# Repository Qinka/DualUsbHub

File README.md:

# DualUsbHub
Dual host plugin usb 2.0 HUB

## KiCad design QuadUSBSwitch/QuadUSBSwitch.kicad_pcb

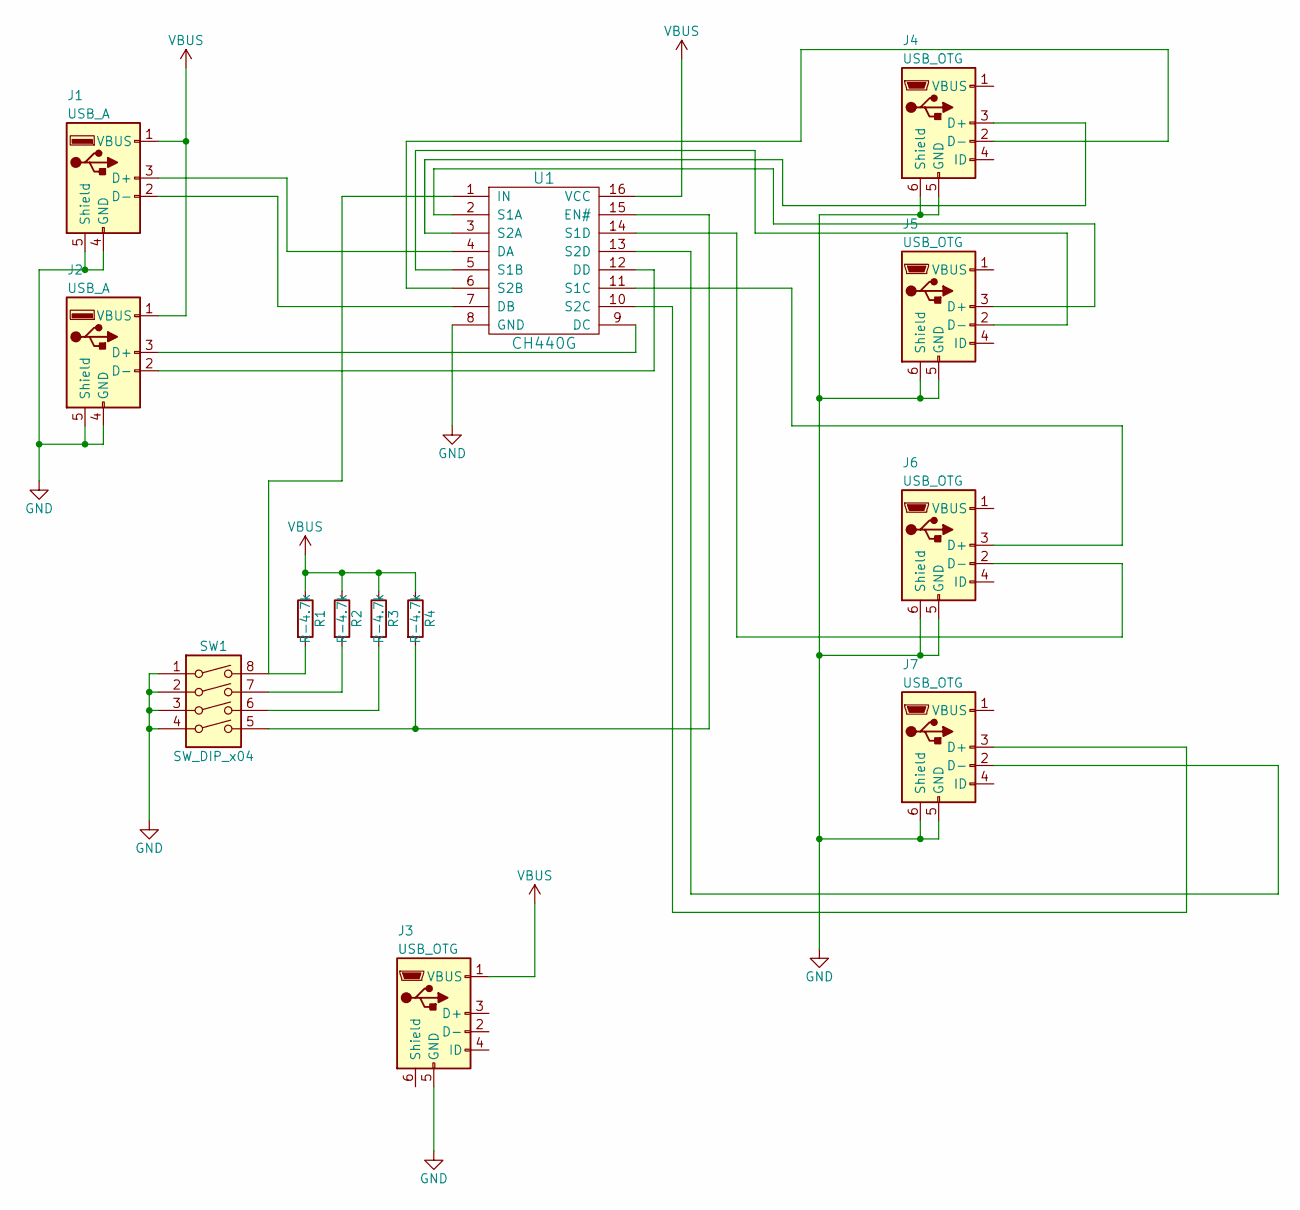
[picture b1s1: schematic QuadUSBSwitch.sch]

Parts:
J1, J2: USB_A
J3, J4, J5, J6, J7: USB_OTG; USB_Micro-B
R1, R2, R3, R4: R-4.7k; R_0805
SW1: SW_DIP_x04; SW_DIP_x4_W8.61mm_Slide_LowProfile
U1: CH440G; ch440g

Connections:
GND: J1.4 (GND), J1.5 (Shield), J2.4 (GND), J2.5 (Shield), J3.5 (GND), J4.5 (GND), J4.6 (Shield), J5.5 (GND), J5.6 (Shield), J6.5 (GND), J6.6 (Shield), J7.5 (GND), J7.6 (Shield), SW1.1, SW1.2, SW1.3, SW1.4, U1.8 (GND)
unnamed: J1.2 (D-), U1.7 (DB)
unnamed: J1.3 (D+), U1.4 (DA)
unnamed: J2.2 (D-), U1.12 (DD)
unnamed: J2.3 (D+), U1.9 (DC)
unnamed: J4.2 (D-), U1.6 (S2B)
unnamed: J4.3 (D+), U1.3 (S2A)
unnamed: J5.2 (D-), U1.5 (S1B)
unnamed: J5.3 (D+), U1.2 (S1A)
unnamed: J6.2 (D-), U1.14 (S1D)
unnamed: J6.3 (D+), U1.11 (S1C)
unnamed: J7.2 (D-), U1.13 (S2D)
unnamed: J7.3 (D+), U1.10 (S2C)
unnamed: R1.2, SW1.8, U1.1 (IN)
unnamed: R2.2, SW1.7
unnamed: R3.2, SW1.6
unnamed: R4.2, SW1.5, U1.15 (EN#)
VBUS: J1.1 (VBUS), J2.1 (VBUS), J3.1 (VBUS), R1.1, R2.1, R3.1, R4.1, U1.16 (VCC)

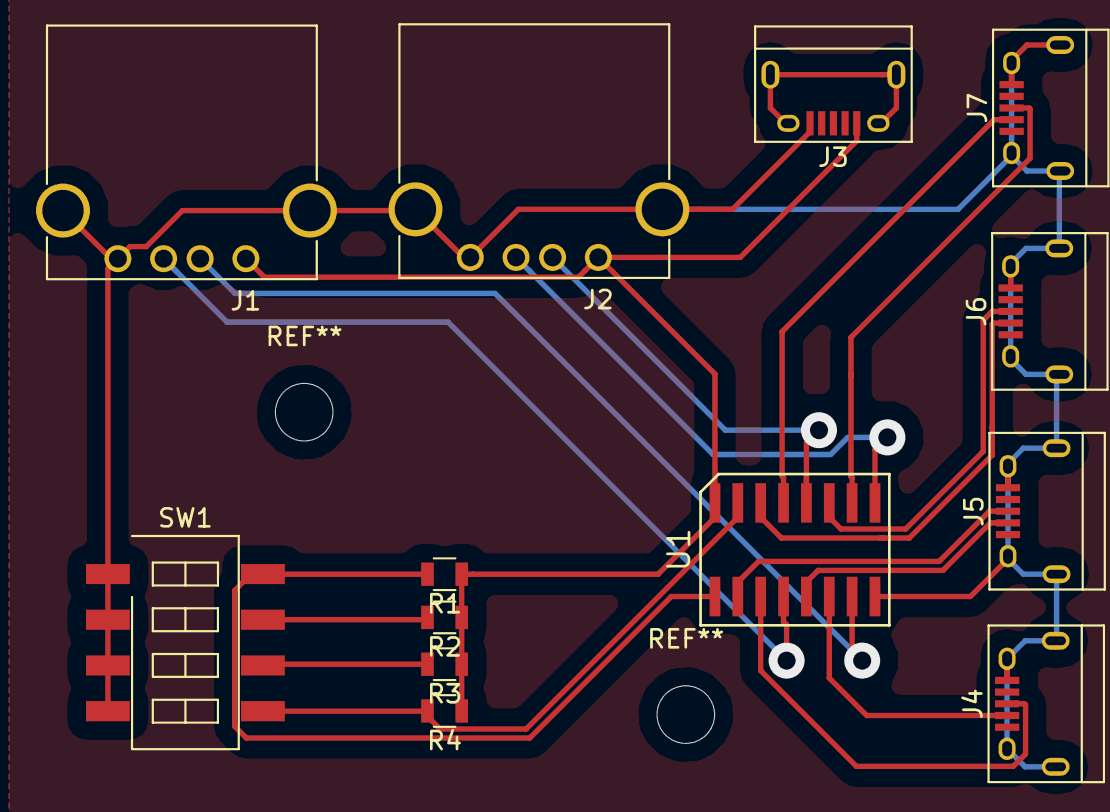
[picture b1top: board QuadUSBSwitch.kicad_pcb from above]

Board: 2 copper layers, 13 parts (0 on the bottom side), 18 nets.

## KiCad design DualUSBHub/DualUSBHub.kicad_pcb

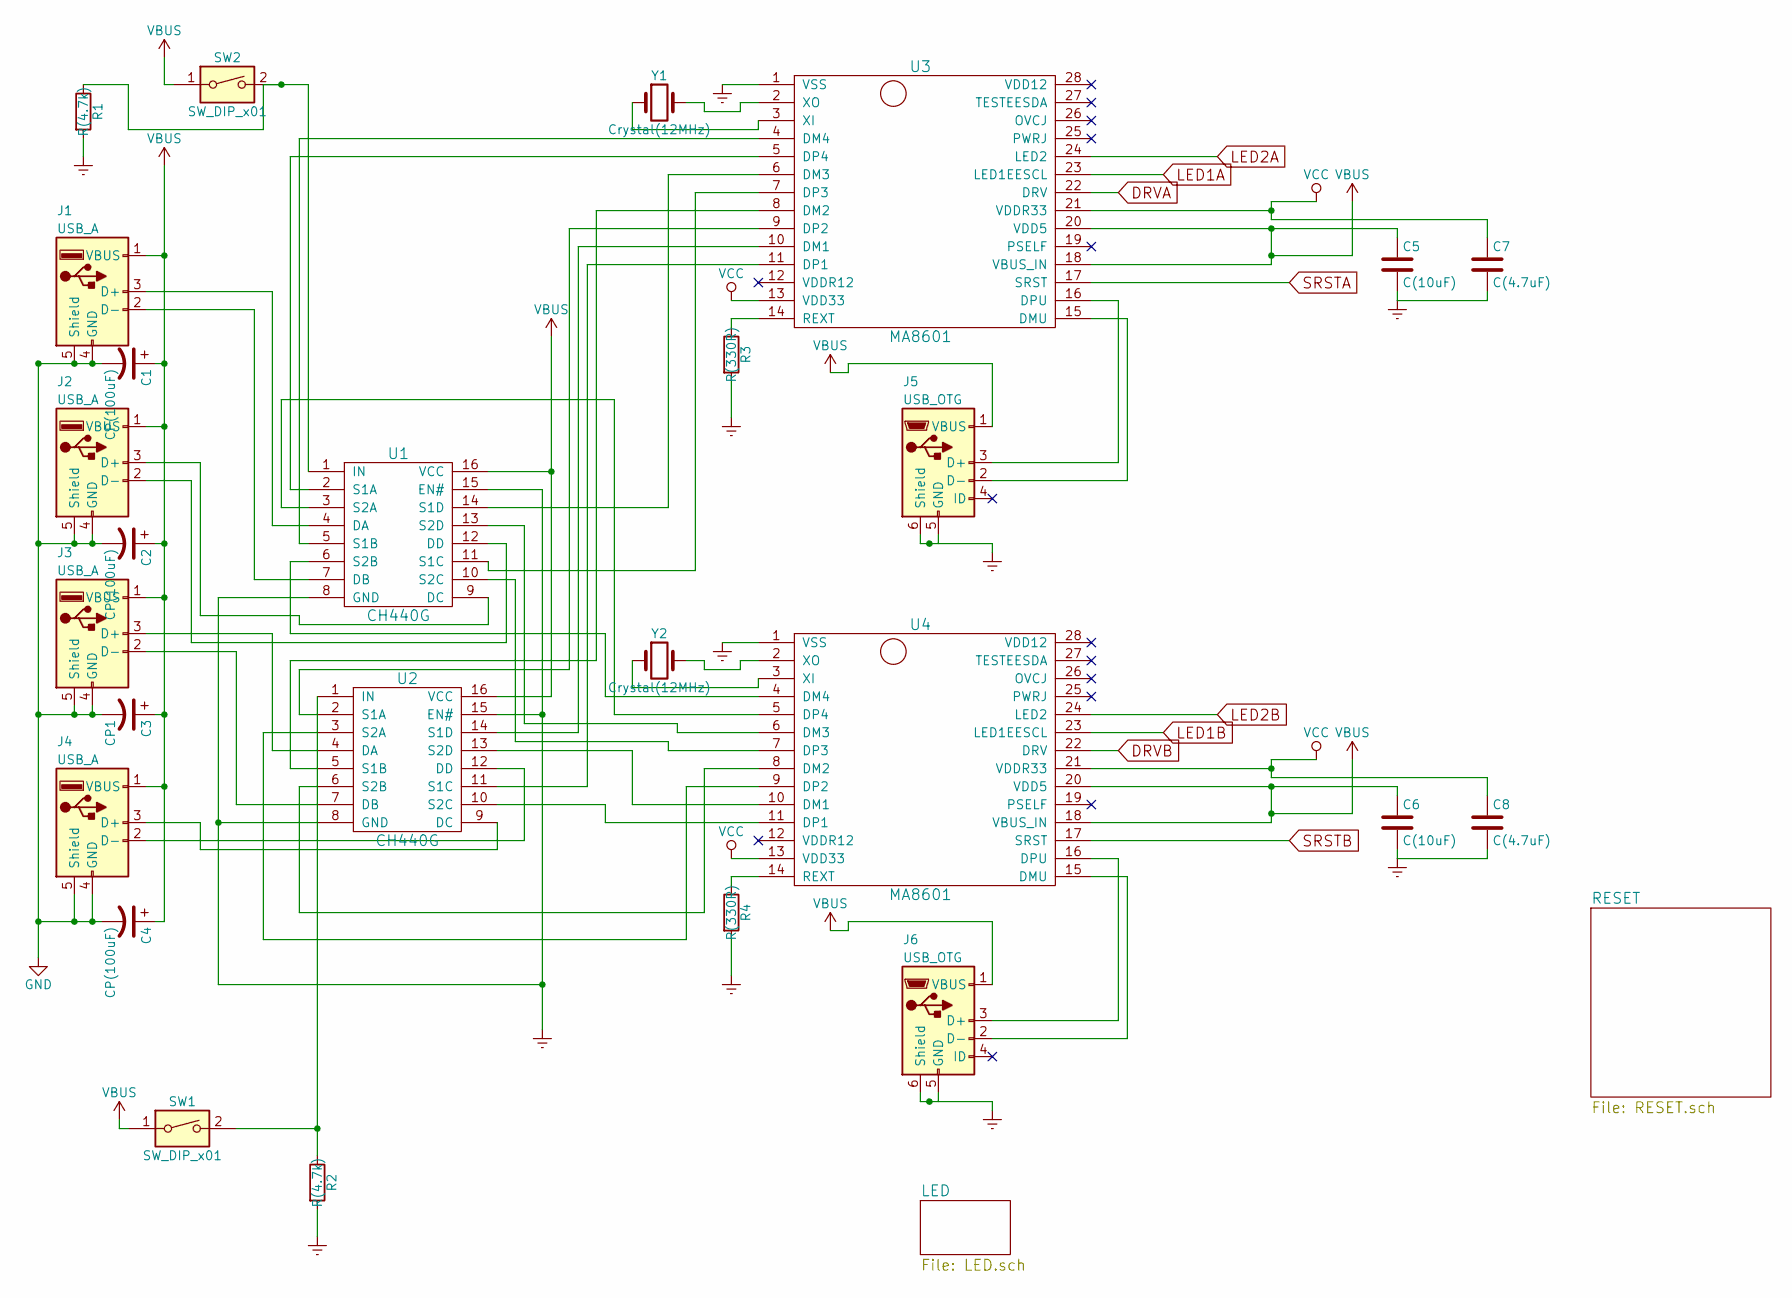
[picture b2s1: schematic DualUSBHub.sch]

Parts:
C1, C2, C4: CP(100uF); CP_Elec_6.3x4.5
C3: CP1; CP_Elec_6.3x4.5
C5, C6: C(10uF); C_0805
C7, C8: C(4.7uF); C_0805
J1, J2, J3, J4: USB_A
J5, J6: USB_OTG; USB_Micro-B
R1, R2: R(4.7k); R_0805
R3, R4: R(330R); R_0805
SW1, SW2: SW_DIP_x01; SW_DIP_x1_W7.62mm_Slide_Copal_CHS-B
U1, U2: CH440G; ch440g
U3, U4: MA8601; ma8601
Y1, Y2: Crystal(12MHz); Crystal_SMD_HC49-SD

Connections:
DRVA: U3.22 (DRV); also elsewhere on the board
DRVB: U4.22 (DRV); also elsewhere on the board
Earth: C5.2, C6.2, C7.2, C8.2, J5.6 (Shield), J6.6 (Shield), R1.2, R2.2, R3.2, R4.2, U1.8 (GND), U1.15 (EN#), U2.8 (GND), U2.15 (EN#), U3.1 (VSS), U4.1 (VSS); also elsewhere on the board
GND: C1.2, C2.2, C3.2, C4.2, J1.4 (GND), J1.5 (Shield), J2.4 (GND), J2.5 (Shield), J3.4 (GND), J3.5 (Shield), J4.4 (GND), J4.5 (Shield)
LED1A: U3.23 (LED1EESCL); also elsewhere on the board
LED1B: U4.23 (LED1EESCL); also elsewhere on the board
LED2A: U3.24 (LED2); also elsewhere on the board
LED2B: U4.24 (LED2); also elsewhere on the board
unnamed: J1.2 (D-), U1.7 (DB)
unnamed: J1.3 (D+), U1.4 (DA)
unnamed: J2.2 (D-), U1.12 (DD)
unnamed: J2.3 (D+), U1.9 (DC)
unnamed: J3.2 (D-), U2.7 (DB)
unnamed: J3.3 (D+), U2.4 (DA)
unnamed: J4.2 (D-), U2.12 (DD)
unnamed: J4.3 (D+), U2.9 (DC)
unnamed: J5.2 (D-), U3.15 (DMU)
unnamed: J5.3 (D+), U3.16 (DPU)
unnamed: J6.2 (D-), U4.15 (DMU)
unnamed: J6.3 (D+), U4.16 (DPU)
unnamed: R1.1, SW2.2, U1.1 (IN)
unnamed: R2.1, SW1.2, U2.1 (IN)
unnamed: R3.1, U3.14 (REXT)
unnamed: R4.1, U4.14 (REXT)
unnamed: U1.2 (S1A), U3.5 (DP4)
unnamed: U1.3 (S2A), U4.5 (DP4)
unnamed: U1.5 (S1B), U3.4 (DM4)
unnamed: U1.6 (S2B), U4.4 (DM4)
unnamed: U1.10 (S2C), U4.7 (DP3)
unnamed: U1.11 (S1C), U3.7 (DP3)
unnamed: U1.13 (S2D), U4.6 (DM3)
unnamed: U1.14 (S1D), U3.6 (DM3)
unnamed: U2.2 (S1A), U3.9 (DP2)
unnamed: U2.3 (S2A), U4.9 (DP2)
unnamed: U2.5 (S1B), U3.8 (DM2)
unnamed: U2.6 (S2B), U4.8 (DM2)
unnamed: U2.10 (S2C), U4.11 (DP1)
unnamed: U2.11 (S1C), U3.11 (DP1)
unnamed: U2.13 (S2D), U4.10 (DM1)
unnamed: U2.14 (S1D), U3.10 (DM1)
unnamed: U3.2 (XO), Y1.2
unnamed: U3.3 (XI), Y1.1
unnamed: U4.2 (XO), Y2.2
unnamed: U4.3 (XI), Y2.1
SRSTA: U3.17 (SRST); also elsewhere on the board
SRSTB: U4.17 (SRST); also elsewhere on the board
VBUS: C1.1, C2.1, C3.1, C4.1, C5.1, C6.1, J1.1 (VBUS), J2.1 (VBUS), J3.1 (VBUS), J4.1 (VBUS), J5.1 (VBUS), J6.1 (VBUS), SW1.1, SW2.1, U1.16 (VCC), U2.16 (VCC), U3.18 (VBUS_IN), U3.20 (VDD5), U4.18 (VBUS_IN), U4.20 (VDD5); also elsewhere on the board
VCC: C7.1, C8.1, U3.13 (VDD33), U3.21 (VDDR33), U4.13 (VDD33), U4.21 (VDDR33); also elsewhere on the board

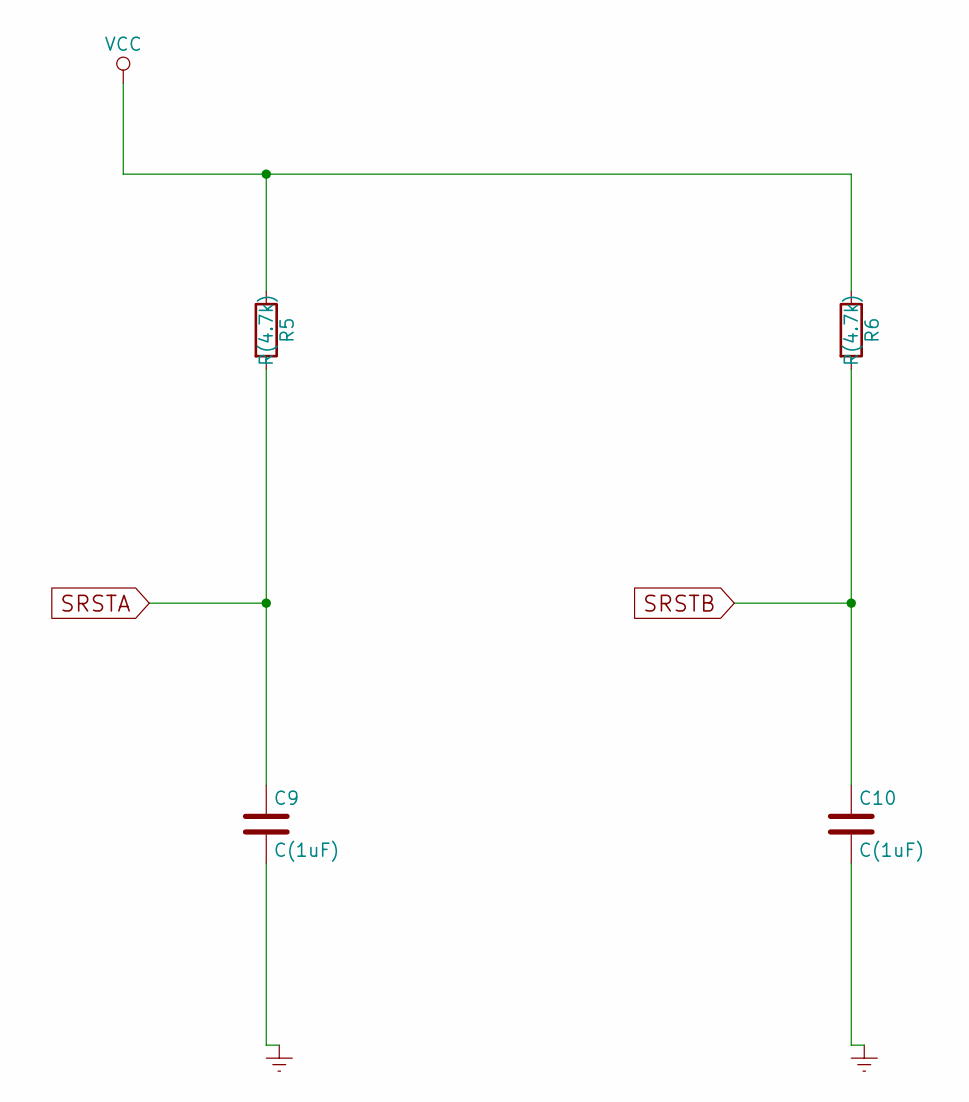
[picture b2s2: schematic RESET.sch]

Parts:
C9, C10: C(1uF); C_0805
R5, R6: R(4.7k); R_0805

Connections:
Earth: C9.2, C10.2; also elsewhere on the board
SRSTA: C9.1, R5.2; also elsewhere on the board
SRSTB: C10.1, R6.2; also elsewhere on the board
VCC: R5.1, R6.1; also elsewhere on the board

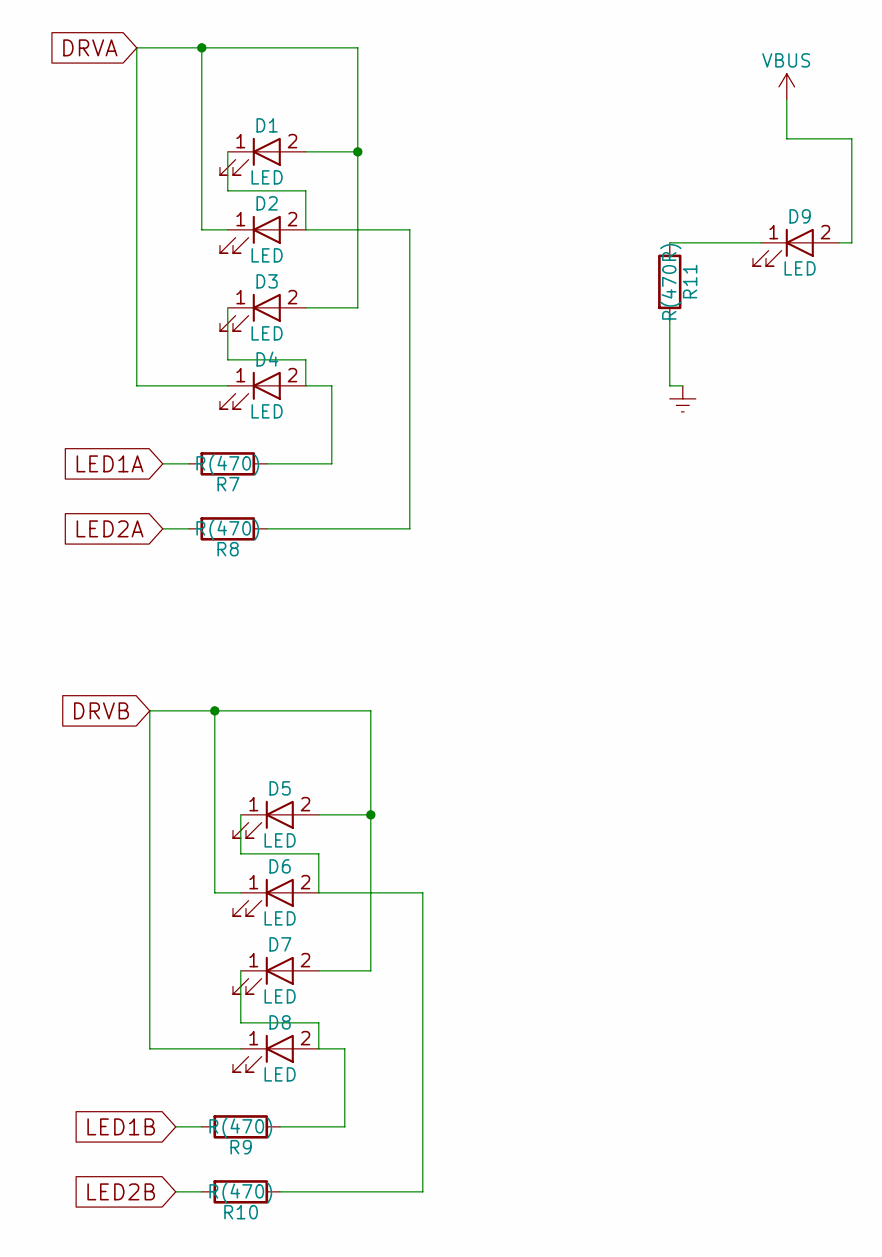
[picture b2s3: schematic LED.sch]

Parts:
D1, D2, D3, D4, D5, D6, D7, D8, D9: LED; LED_0805
R7, R8, R9, R10: R(470); R_0805
R11: R(470R); R_0805

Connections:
DRVA: D1.2 (A), D2.1 (K), D3.2 (A), D4.1 (K); also elsewhere on the board
DRVB: D5.2 (A), D6.1 (K), D7.2 (A), D8.1 (K); also elsewhere on the board
Earth: R11.2; also elsewhere on the board
LED1A: R7.2; also elsewhere on the board
LED1B: R9.2; also elsewhere on the board
LED2A: R8.2; also elsewhere on the board
LED2B: R10.2; also elsewhere on the board
unnamed: D1.1 (K), D2.2 (A), R8.1
unnamed: D3.1 (K), D4.2 (A), R7.1
unnamed: D5.1 (K), D6.2 (A), R10.1
unnamed: D7.1 (K), D8.2 (A), R9.1
unnamed: D9.1 (K), R11.1
VBUS: D9.2 (A); also elsewhere on the board

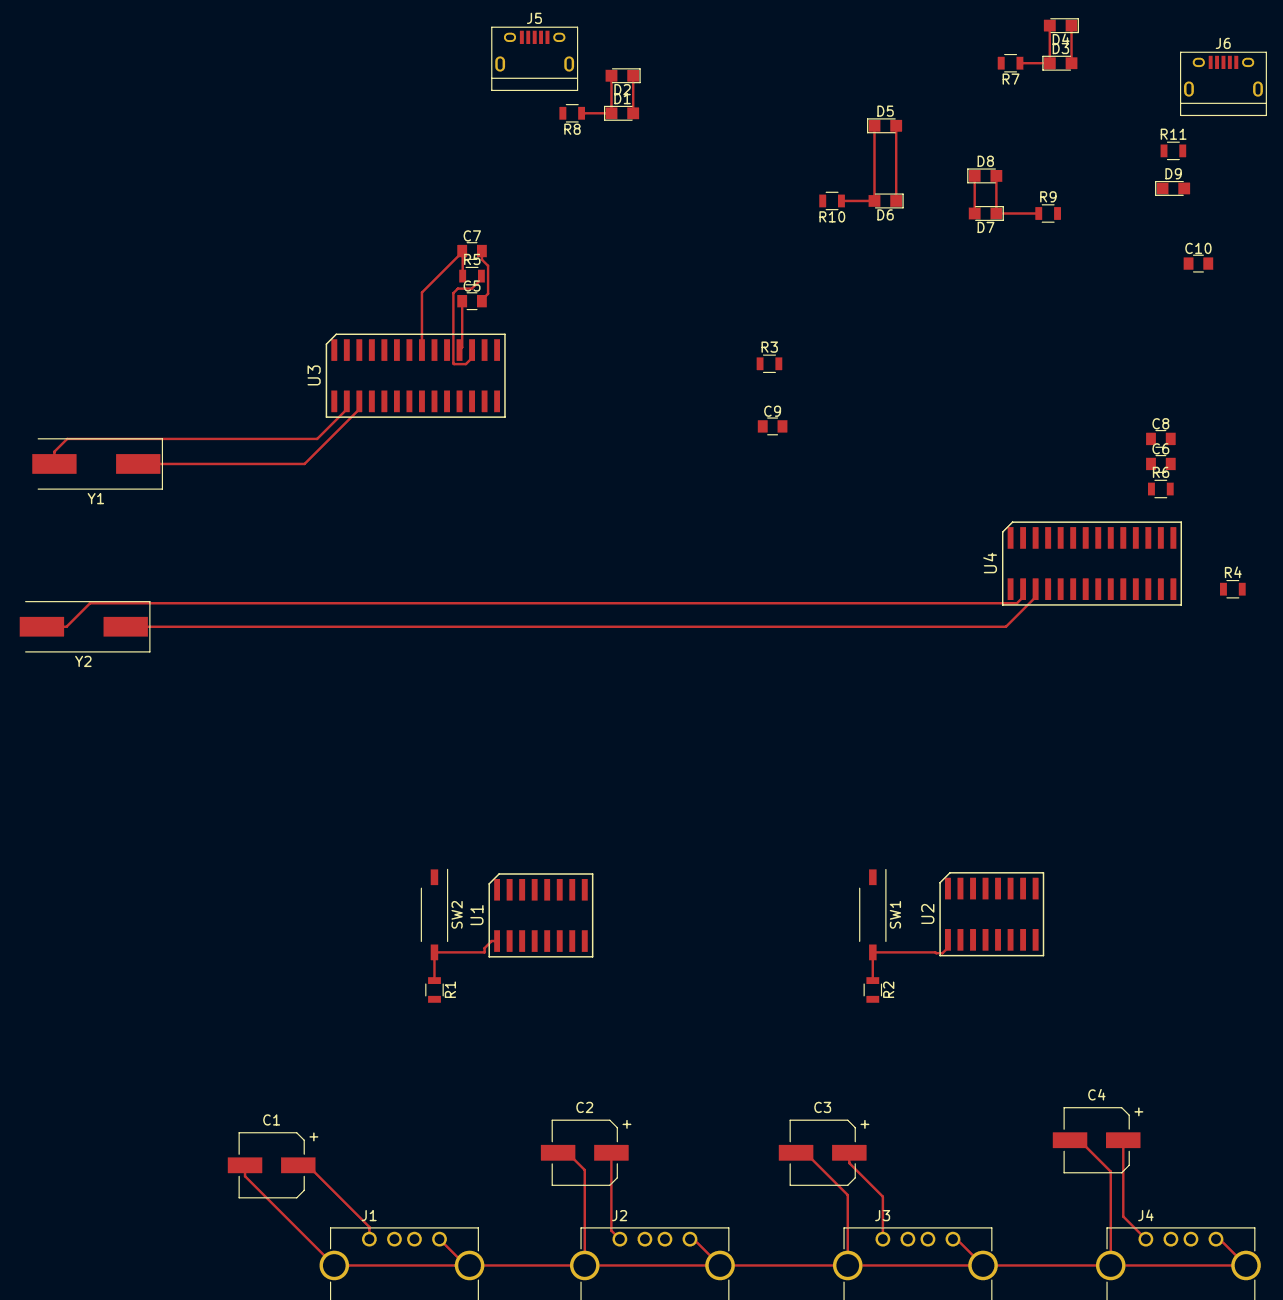
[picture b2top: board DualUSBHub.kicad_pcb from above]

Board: 2 copper layers, 44 parts (0 on the bottom side), 53 nets.

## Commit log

2018-02-22 init
2018-02-23 add the schematic diagrams and packagings
2018-03-04 update; add a dual switch
2018-03-06 update; a test dual layer one is ready
2018-03-08 update;
